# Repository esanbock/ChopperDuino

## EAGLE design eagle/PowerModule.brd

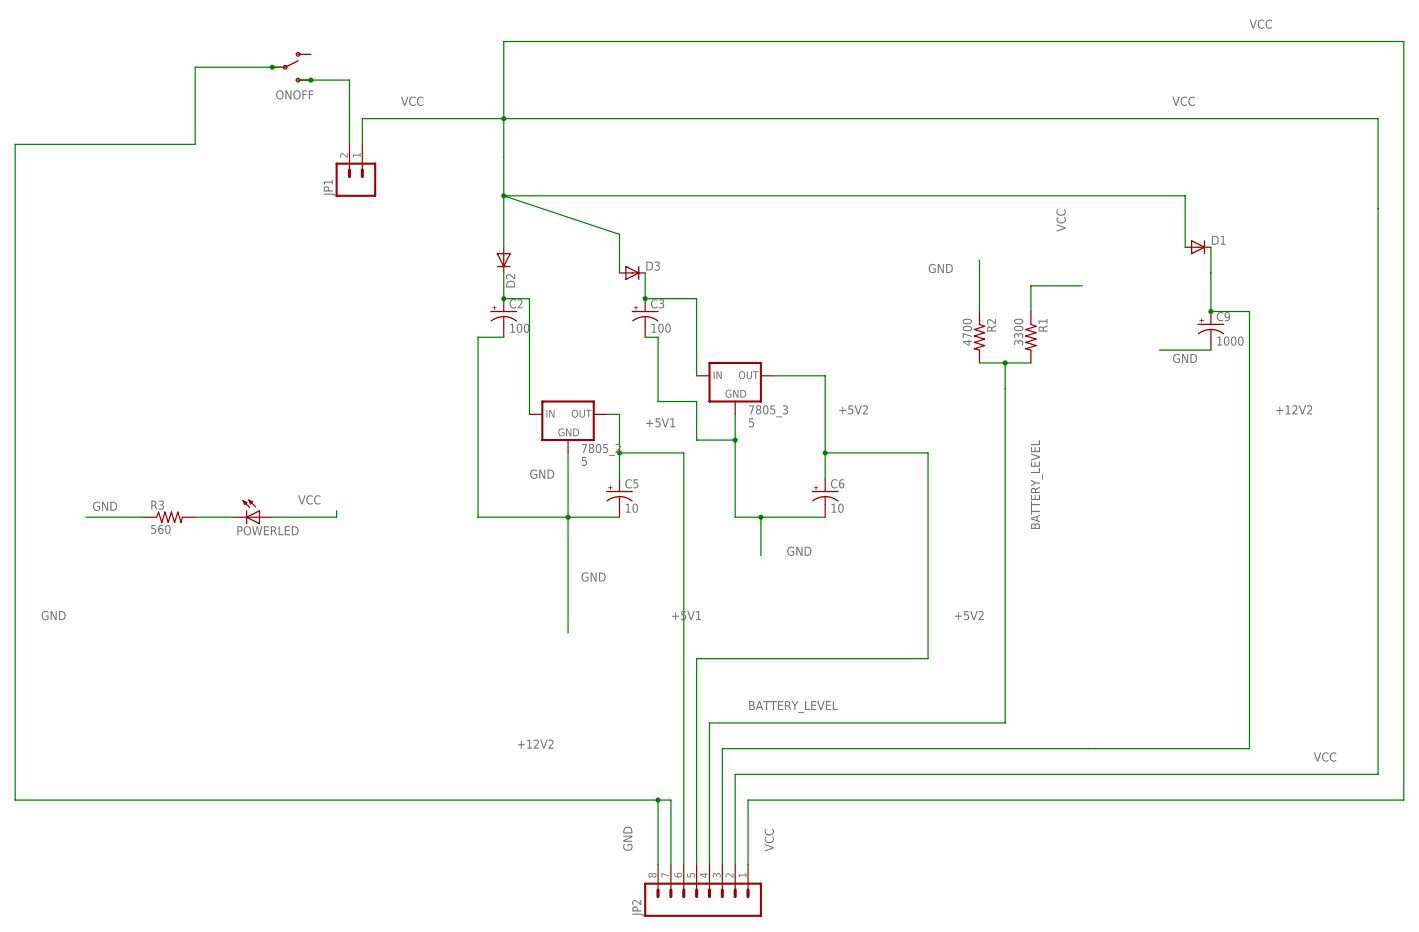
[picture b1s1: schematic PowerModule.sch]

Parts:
7805_2, 7805_3: 5; TO220-IGO
C2, C3: 100; CPOL-RADIAL-100UF-25V
C5, C6: 10; CPOL-RADIAL-10UF-25V
C9: 1000; CPOL-RADIAL-100UF-25V
D1, D2, D3: DIODEPTH; DIODE-1N4001
JP1: M025MM; SCREWTERMINAL-5MM-2
JP2: M081X08; 1X08
ONOFF: SWITCH-SPSTPTH; SWITCH-SPDT
POWERLED: LED3MM
R1: 3300; AXIAL-0.4
R2: 4700; AXIAL-0.4
R3: 560; AXIAL-0.4

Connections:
+5V1: 7805_2.OUT, C5.1 (+), JP2.6
+5V2: 7805_3.OUT, C6.1 (+), JP2.5
+12V2: C9.1 (+), D1.C, JP2.3
BATTERY_LEVEL: JP2.4, R1.P$2 (2), R2.P$2 (2)
GND: 7805_2.GND, 7805_3.GND, C2.2 (-), C3.2 (-), C5.2 (-), C6.2 (-), C9.2 (-), JP2.7, JP2.8, ONOFF.2, R2.P$1 (1), R3.P$1 (1)
unnamed: 7805_2.IN, C2.1 (+), D2.C
unnamed: 7805_3.IN, C3.1 (+), D3.C
unnamed: JP1.2, ONOFF.3 (S)
unnamed: POWERLED.K (C), R3.P$2 (2)
VCC: D1.A, D2.A, D3.A, JP1.1, JP2.1, JP2.2, POWERLED.A, R1.P$1 (1)

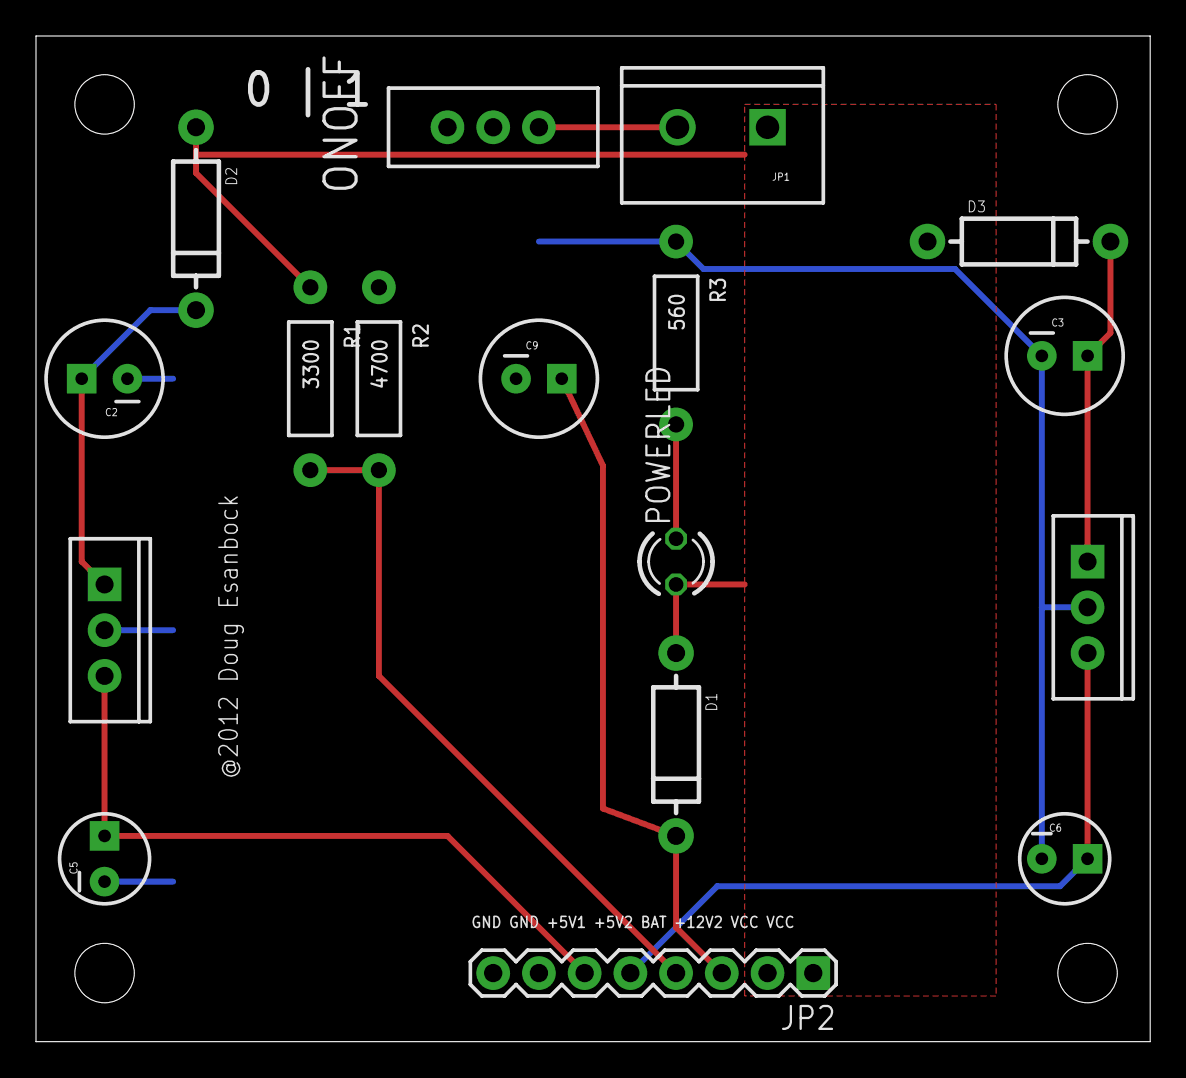
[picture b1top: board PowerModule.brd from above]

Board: 2 copper layers, 61.9 x 55.9 mm, 21 parts (0 on the bottom side), 10 nets.

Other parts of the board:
U$1, U$2, U$3, U$4: STAND-OFF

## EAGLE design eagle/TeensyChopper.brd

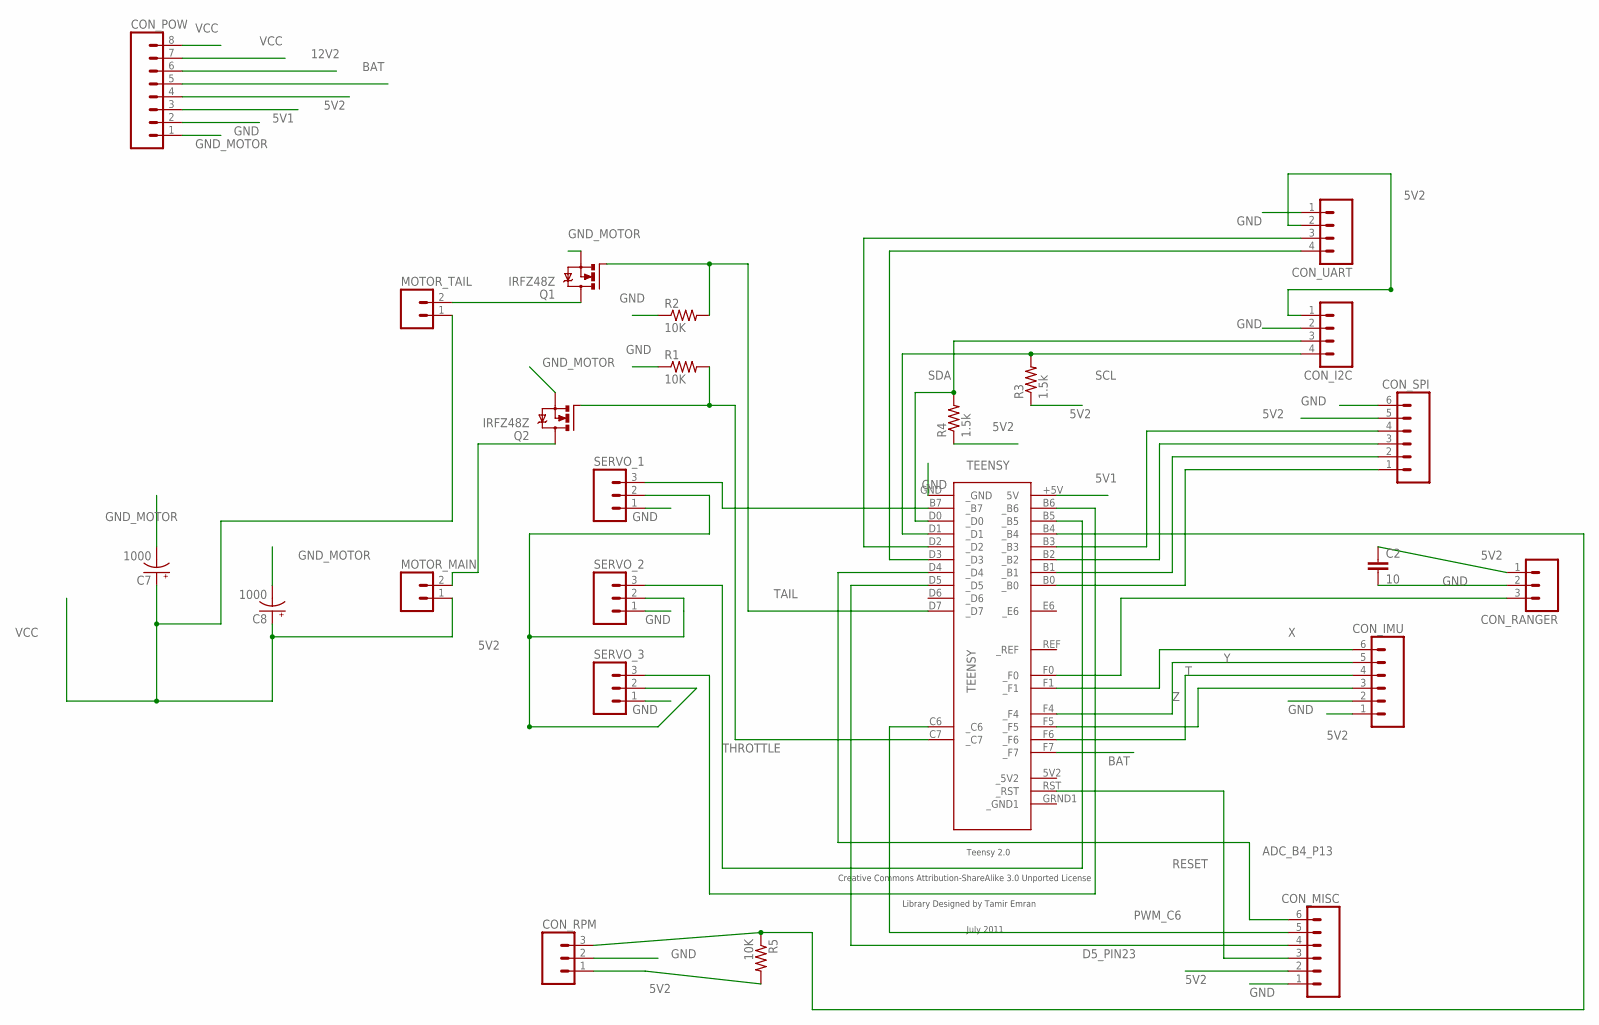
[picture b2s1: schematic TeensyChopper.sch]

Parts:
C2: 10; CAP-PTH-SMALL-KIT
C7, C8: 1000; CPOL-RADIAL-1000UF-25V
CON_I2C: M04PTH; 1X04
CON_IMU: M06LOCK; 1X06_LOCK
CON_MISC: M06LOCK; 1X06_LOCK
CON_POW: M081X08; 1X08
CON_RANGER: M03PTH; 1X03
CON_RPM: M03PTH; 1X03
CON_SPI: M06LOCK; 1X06_LOCK
CON_UART: M04PTH; 1X04
MOTOR_MAIN: M025MM; SCREWTERMINAL-5MM-2
MOTOR_TAIL: M025MM; SCREWTERMINAL-5MM-2
Q1, Q2: IRFZ48Z; TO220BH
R1, R2, R5: 10K; AXIAL-0.4
R3, R4: 1.5k; AXIAL-0.4
SERVO_1, SERVO_2, SERVO_3: M03PTH; 1X03
TEENSY: TEENSY

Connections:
5V1: CON_POW.3, TEENSY.+5V (5V)
5V2: C2.1, CON_I2C.1, CON_IMU.1, CON_MISC.2, CON_POW.4, CON_RANGER.1, CON_RPM.1, CON_SPI.5, CON_UART.2, R3.P$1 (1), R4.P$1 (1), R5.P$2 (2), SERVO_1.2, SERVO_2.2, SERVO_3.2
12V2: CON_POW.6
ADC_B4_P13: CON_MISC.6, TEENSY.D4 (_D4)
BAT: CON_POW.5, TEENSY.F7 (_F7)
D5_PIN23: CON_MISC.4, TEENSY.D5 (_D5)
GND: C2.2, CON_I2C.2, CON_IMU.2, CON_MISC.1, CON_POW.2, CON_RANGER.2, CON_RPM.2, CON_SPI.6, CON_UART.1, R1.P$1 (1), R2.P$1 (1), SERVO_1.1, SERVO_2.1, SERVO_3.1, TEENSY.GND (_GND)
GND_MOTOR: C7.2 (-), C8.2 (-), CON_POW.1, Q1.S, Q2.S
unnamed: CON_RANGER.3, TEENSY.F0 (_F0)
unnamed: SERVO_1.3, TEENSY.B7 (_B7)
unnamed: CON_SPI.1, TEENSY.B0 (_B0)
unnamed: CON_SPI.2, TEENSY.B1 (_B1)
unnamed: CON_RPM.3, R5.P$1 (1), TEENSY.B4 (_B4)
unnamed: CON_SPI.3, TEENSY.B2 (_B2)
unnamed: MOTOR_MAIN.2, Q2.D
unnamed: MOTOR_TAIL.2, Q1.D
unnamed: SERVO_3.3, TEENSY.B6 (_B6)
unnamed: CON_SPI.4, TEENSY.B3 (_B3)
unnamed: SERVO_2.3, TEENSY.B5 (_B5)
PWM_C6: CON_MISC.5, TEENSY.C6 (_C6)
RESET: CON_MISC.3, TEENSY.RST (_RST)
RX: CON_UART.3, TEENSY.D2 (_D2)
SCL: CON_I2C.4, R3.P$2 (2), TEENSY.D1 (_D1)
SDA: CON_I2C.3, R4.P$2 (2), TEENSY.D0 (_D0)
T: CON_IMU.4, TEENSY.F6 (_F6)
TAIL: Q1.G, R2.P$2 (2), TEENSY.D7 (_D7)
THROTTLE: Q2.G, R1.P$2 (2), TEENSY.C7 (_C7)
TX: CON_UART.4, TEENSY.D3 (_D3)
VCC: C7.1 (+), C8.1 (+), CON_POW.7, CON_POW.8, MOTOR_MAIN.1, MOTOR_TAIL.1
X: CON_IMU.6, TEENSY.F1 (_F1)
Y: CON_IMU.5, TEENSY.F4 (_F4)
Z: CON_IMU.3, TEENSY.F5 (_F5)

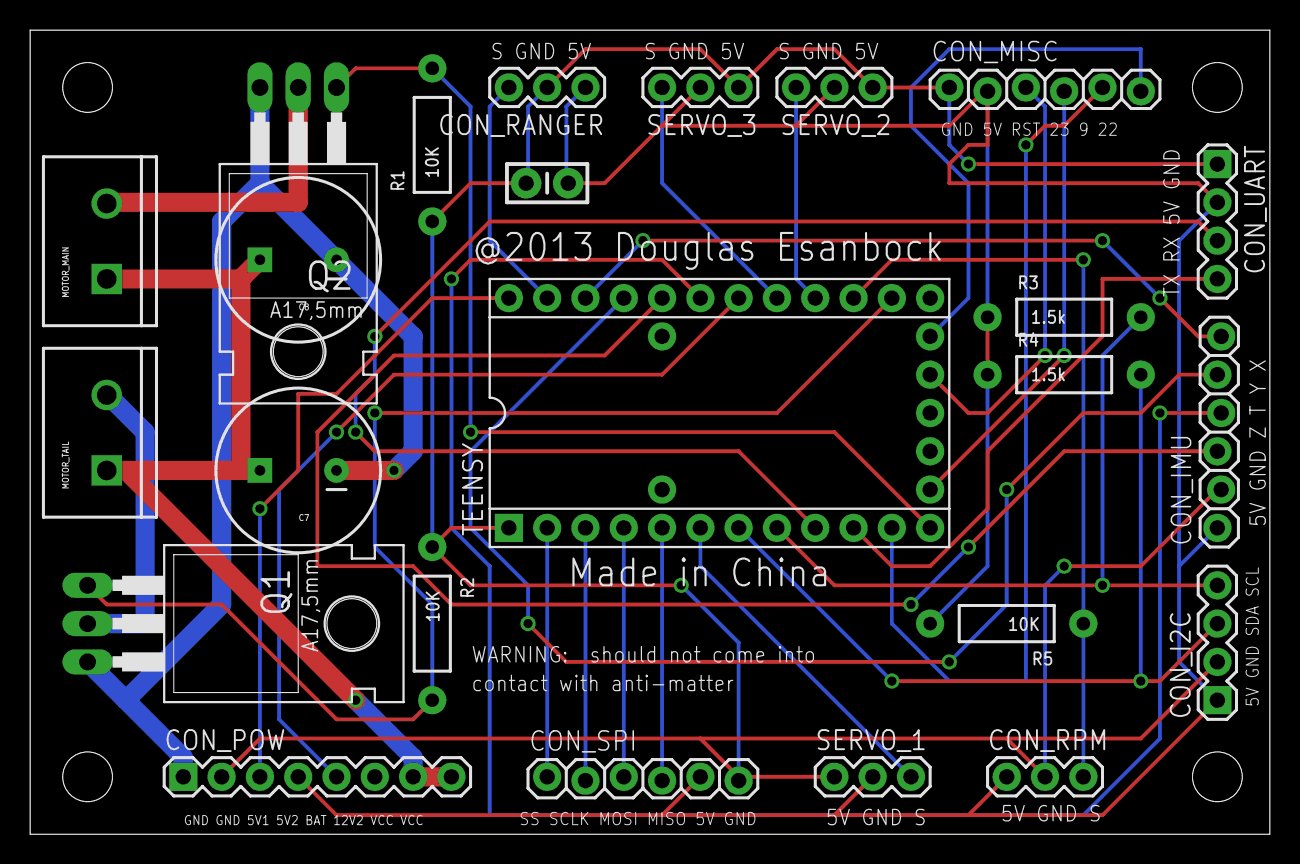
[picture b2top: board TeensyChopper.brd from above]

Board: 2 copper layers, 82.2 x 53.3 mm, 28 parts (0 on the bottom side), 31 nets.

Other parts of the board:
U$1, U$2, U$3, U$4: STAND-OFF

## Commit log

2015-01-03 adding Arduino code
2015-01-03 adding schematics
2015-01-03 LaenPCB rules
2015-01-03 updating .gitignore
    removing svn files
2015-02-07 plugging in PID library
2015-02-08 debugging the IMU
2015-02-08 more IMU debugging - pullup resistors
2015-02-08 misc cleanup
2015-02-09 higher baud rates
2015-02-09 doing averages, switching back to regular non-pullup pins
2015-02-09 averaging 100 readings (probably overkill)
2015-02-09 40 samples per average
2015-02-10 switching to moving average to save memory
2015-02-10 getting rid of per MS stuff
2015-02-10 cleanup unused variables, cleanup formatting
2015-02-10 removing commented out code
2015-02-10 .gitignoring the eagle backup files
2015-02-16 Correct combination of pitch, bank, and roll for swashplate
2015-02-16 starting RPM sensor
2015-02-17 refactoring nav to process commands
    (cleaning up code)
2015-02-17 cleaning up emergency landing code
2015-02-17 cleanup
2017-04-08 using correct term for collective
2017-04-23 refactoring function locations
2017-04-29 rely on the PID for changes to the bank
2017-04-29 flipping the PID between manual & auto during overides
2017-04-30 comments and whitespace
2017-04-30 replace bank with roll
2017-04-30 refactoring sketch into multiple files
2017-04-30 null char message
2017-04-30 efficient blinker
2017-05-01 remove superfluous checks, making collective data type a double
2017-05-01 switching x & y
2017-05-01 voltage monitor
2017-05-01 y pid
2017-05-03 collective & throttle fixes
2017-05-04 adding a simple controller to isolate PID logic problems
2017-05-04 renames, etc
2017-05-04 sending strings in batches
2017-05-04 more reliable voltage reads (slower)
2017-05-04 cleanup (virtual destructors)
2017-05-04 comms improvement, flipped logic
2017-05-06 sending new home
2017-05-06 reversed the servos
2017-05-06 optional sends
2017-05-06 dumping motors
2017-05-07 splitting IMUs into simple and moving average one
2017-05-07 making pings optional
2017-05-07 optional emergency landing
2017-05-08 pid command parsing
2017-05-08 adding real-time PID tuning
2017-05-08 switching to comma delimeted
2017-05-08 conversion
2017-05-09 no longer messing with bank when elevators change
2017-05-09 flushing buffs every send
2017-05-09 controller logic
2017-05-09 Revert "flushing buffs every send"
    This reverts commit dcb2adde547d858603396c64b0b5eb4e6476d993.
2017-05-11 PID & IMU improvements
2017-06-01 getcharblocking no longer blocks indefinetely. Now waits only 10 ms for a character
2017-06-01 only process nav sequences every 10 milliseconds
2019-01-12 separate command for lift/collective
2019-01-12 adding collective override

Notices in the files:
parts and their libraries:
teensy: Licensed Under Creative Commons
SparkFun-Resistors: Licensing: CC v3.0 Share-Alike You are welcome to use this library for commercial purposes.
teensy: Creative Commons Attribution-ShareAlike 3.0 Unported License
